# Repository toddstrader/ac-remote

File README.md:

**TODO** Outline the various parts of the project and the tools needed to build

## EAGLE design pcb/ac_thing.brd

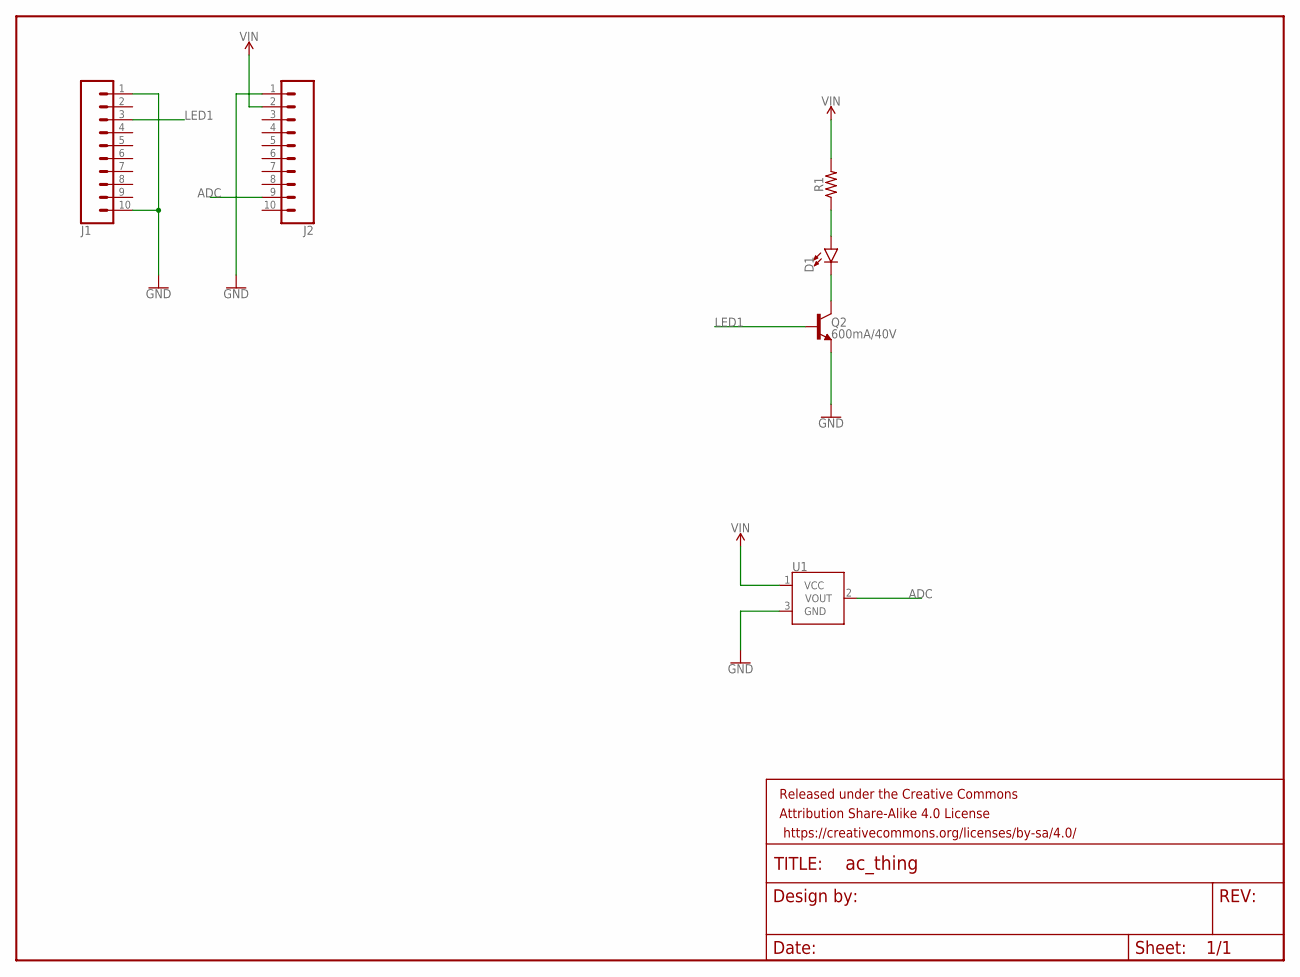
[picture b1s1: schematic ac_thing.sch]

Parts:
D1: LED5MM; LED_5MM
FRAME1: FRAME-LETTER; CREATIVE_COMMONS
J1, J2: CONN_10NO_SILK_PTH_FEMALE; 1X10_NO_SILK
Q2: 600mA/40V; TO-92
R1: AXIAL-0.3
U1: TMP36GT9; TO-92

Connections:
ADC: J2.9, U1.2 (VOUT)
GND: J1.1, J1.10, J2.1, Q2.3 (E), U1.3 (GND)
LED1: J1.3, Q2.2 (B)
unnamed: D1.A, R1.P$1 (1)
unnamed: D1.K (C), Q2.1 (C)
VIN: J2.2, R1.P$2 (2), U1.1 (VCC)

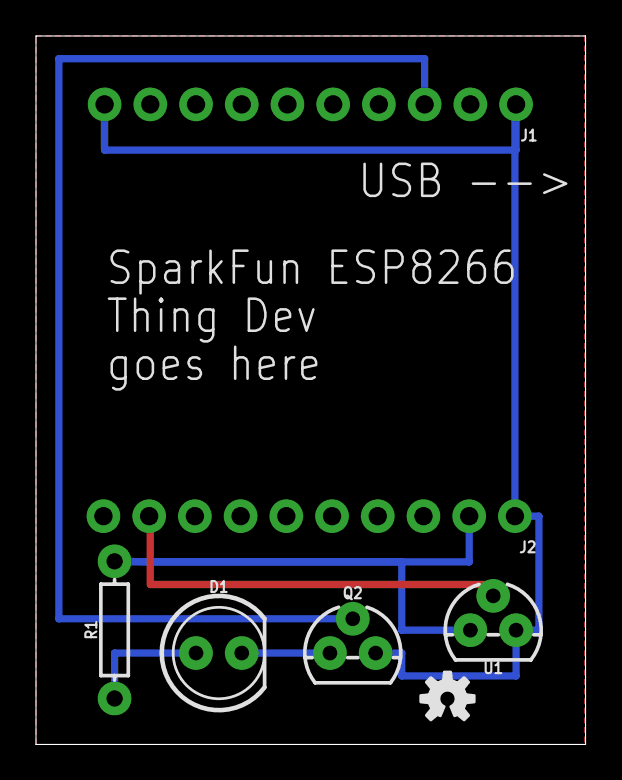
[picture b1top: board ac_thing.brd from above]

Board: 2 copper layers, 30.5 x 39.4 mm, 8 parts (0 on the bottom side), 6 nets.

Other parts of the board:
U$2: OSHW-LOGO-S

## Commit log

2019-03-03 (WIP) Wireless controller for Fujitsu Halcyon AC units
    Mostly working: Arduino, PCB and sample Python controller
    Needs love: Android app

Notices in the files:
parts and their libraries:
SparkFun-Aesthetics: Licensing: Creative Commons ShareAlike 4.0 International - https://creativecommons.org/licenses/by-sa/4.0
SparkFun-Aesthetics: Released under the Creative Commons Attribution Share-Alike 4.0 License
SparkFun-Aesthetics: https://creativecommons.org/licenses/by-sa/4.0
